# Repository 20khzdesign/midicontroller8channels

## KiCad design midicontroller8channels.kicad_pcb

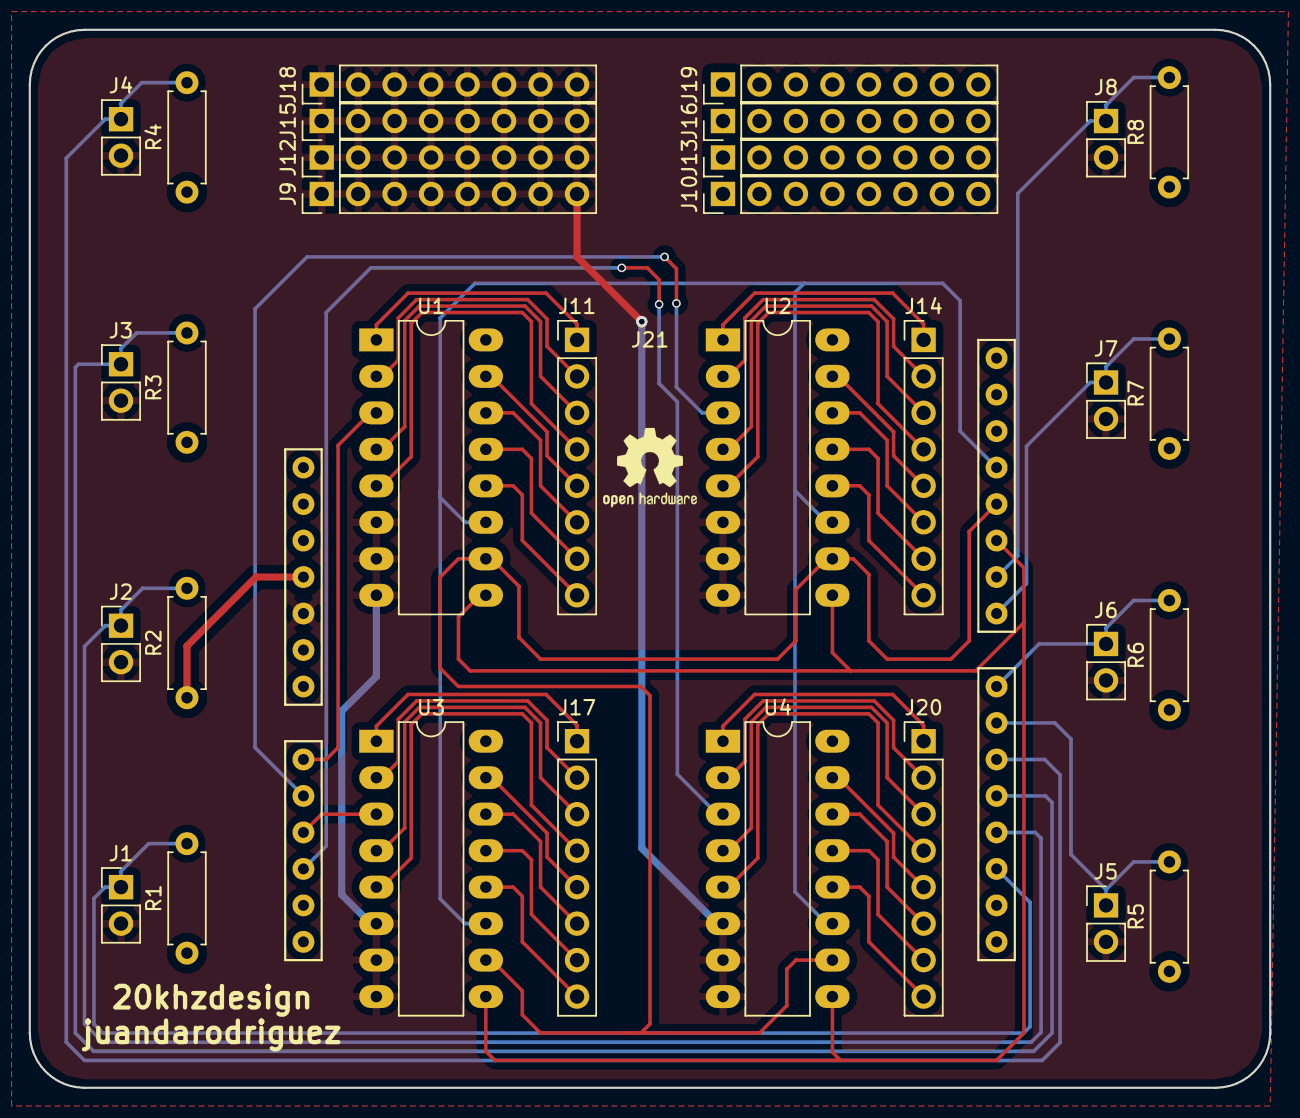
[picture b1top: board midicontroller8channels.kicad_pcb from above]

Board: 2 copper layers, 86.4 x 73.7 mm, 33 parts (0 on the bottom side), 49 nets.

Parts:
J1, J2, J3, J4, J5, J6, J7, J8: Conn_01x02_Male; Pin_Header_Straight_1x02_Pitch2.54mm
J9, J10, J11, J12, J13, J14, J15, J16, J17, J18, J19, J20: Conn_01x08_Male; Pin_Header_Straight_1x08_Pitch2.54mm
J21: arduinoUnoPinout
R1, R2, R3, R4, R5, R6, R7, R8: 2.2k; R_Axial_DIN0207_L6.3mm_D2.5mm_P7.62mm_Horizontal
U1, U2, U3, U4: 4051; DIP-16_W7.62mm_LongPads

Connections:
+5V: J10.1, J10.2, J10.3, J10.4, J10.5, J10.6, J10.7, J10.8, J13.1, J13.2, J13.3, J13.4, J13.5, J13.6, J13.7, J13.8, J16.1, J16.2, J16.3, J16.4, J16.5, J16.6, J16.7, J16.8, J19.1, J19.2, J19.3, J19.4, J19.5, J19.6, J19.7, J19.8, J21.4, R1.1, R2.1, R3.1, R4.1, R5.1, R6.1, R7.1, R8.1, U1.16, U2.16, U3.16, U4.16
A0: J21.8, U1.3
A1: J21.9, U2.3
A2: J21.10, U3.3
A3: J21.11, U4.3
D2: J1.1, J21.16, R1.2
D3: J2.1, J21.17, R2.2
D4: J3.1, J21.18, R3.2
D5: J4.1, J21.19, R4.2
D6: J5.1, J21.20, R5.2
D7: J6.1, J21.21, R6.2
D8: J7.1, J21.22, R7.2
D9: J8.1, J21.23, R8.2
D10: J21.24, U1.9, U2.9, U3.9, U4.9
D11: J21.25, U1.10, U2.10, U3.10, U4.10
D12: J21.26, U1.11, U2.11, U3.11, U4.11
GND: J1.2, J2.2, J3.2, J4.2, J5.2, J6.2, J7.2, J8.2, J9.1, J9.2, J9.3, J9.4, J9.5, J9.6, J9.7, J9.8, J12.1, J12.2, J12.3, J12.4, J12.5, J12.6, J12.7, J12.8, J15.1, J15.2, J15.3, J15.4, J15.5, J15.6, J15.7, J15.8, J18.1, J18.2, J18.3, J18.4, J18.5, J18.6, J18.7, J18.8, J21.5, U1.6, U1.7, U1.8, U2.6, U2.7, U2.8, U3.6, U3.7, U3.8, U4.6, U4.7, U4.8
P0_0: J11.1, U1.1
P0_1: J14.1, U2.1
P0_2: J17.1, U3.1
P0_3: J20.1, U4.1
P1_0: J11.2, U1.2
P1_1: J14.2, U2.2
P1_2: J17.2, U3.2
P1_3: J20.2, U4.2
P2_0: J11.3, U1.4
P2_1: J14.3, U2.4
P2_2: J17.3, U3.4
P2_3: J20.3, U4.4
P3_0: J11.4, U1.5
P3_1: J14.4, U2.5
P3_2: J17.4, U3.5
P3_3: J20.4, U4.5
P4_0: J11.5, U1.15
P4_1: J14.5, U2.15
P4_2: J17.5, U3.15
P4_3: J20.5, U4.15
P5_0: J11.6, U1.14
P5_1: J14.6, U2.14
P5_2: J17.6, U3.14
P5_3: J20.6, U4.14
P6_0: J11.7, U1.13
P6_1: J14.7, U2.13
P6_2: J17.7, U3.13
P6_3: J20.7, U4.13
P7_0: J11.8, U1.12
P7_1: J14.8, U2.12
P7_2: J17.8, U3.12
P7_3: J20.8, U4.12

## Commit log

2017-10-26 commit inicial
2017-10-27 vamooooo
2017-10-27 ay dios
2017-11-04 finalizado
2017-11-06 creo que ahora si está finalizado
2017-11-15 pongo los contornos de zona por fuera del contorno de las placas y rendodeo las esquinas
2017-11-15 añado logo oshw
